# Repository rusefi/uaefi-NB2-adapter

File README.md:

# ABANDONED, NOT TESTED

# uaefi-adapter-template

To be used with https://github.com/rusefi/uaefi

powerted by [rusEFI firmware](https://github.com/rusefi/rusefi)

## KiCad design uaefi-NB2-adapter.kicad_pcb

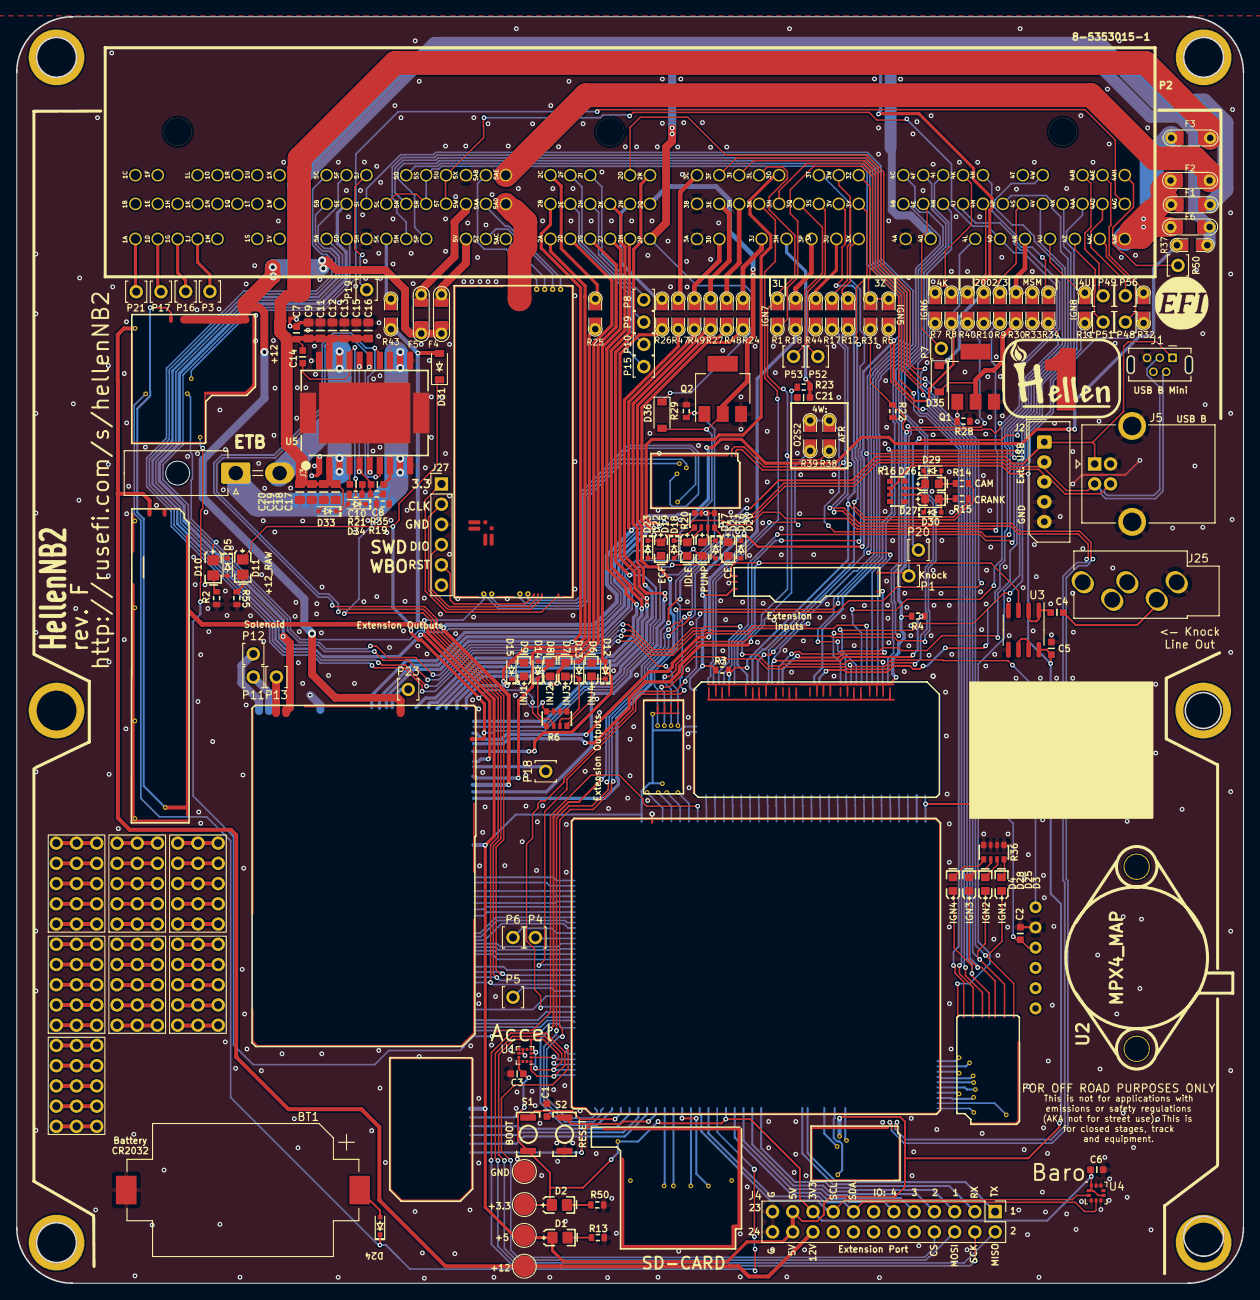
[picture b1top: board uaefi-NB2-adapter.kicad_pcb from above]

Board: 2 copper layers, 154.0 x 159.0 mm, 188 parts (1 on the bottom side), 296 nets.

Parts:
BT1: BATTERY_CR2032; BatteryHolder_Keystone_1060_1x2032
C1, C2, C3, C5, C6, C7, C21: 100n; C0603
C4: 10u; C0603
C8: 6.8n; C0603
C9, C11, C12, C13, C15, C16, C17, C18, C19, C20: 10u; C0805
C10: 10n; C0603
C14: 220n; C0603
D1, D2, D10, D11: LED-GREEN-0805; LED-0805
D3, D4, D25, D28: LED-BLUE-0603; LED-0603
D5, D12, D13, D14, D15, D20, D21, D22, D23, D24, D29, D30, D33, D34: 1N4148WS; SOD-323
D6, D7, D8, D9: LED-RED-0603; LED-0603
D16, D17, D18, D19, D26, D27: LED-WHITE-0603; LED-0603
D31, D35, D36: B5819W; SOD-123
F1, F2, F3, F4, F5, F6: Fuse-Pad-Pad; PAD-1206-PAD
G1, G3: LOGO
G2: DISCLAIMER; Off_Road_Disclaimer
G4, G5, G6, G7, G9, G11, G12: PROTO_AREA
J1: USB_B_Mini; USB-MINI-B-VERTICAL
J2: Conn_01x05_Male; Molex_SPOX_5267-05A_1x05_P2.50mm_Vertical
J3: MiniFit; Molex-39301020
J4: Conn_02x12_Odd_Even; PinHeader_2x12_P2.54mm_Vertical
J5: USB_B
J11, J13, J14, J15, J16, J17: Conn_01x01; MountingHole_4.5mm_Pad
J19, J20, J21, J22, J24: Conn_01x01; TestPoint_Pad_D2.0mm
J25: AudioJack3_SwitchTR; Jack_3.5mm_PJ-3250-5A
J27: Conn_01x06; PinHeader_1x06_P2.54mm_Vertical
M1: Module-input-0.1; input
M2: Module-ign8-0.2; ign8
M3: Module-mcu-0.6; mcu
M4: Module-sd-0.1; sd
M5: Module-output-0.3; output
M6: Module-dinput4-0.1; dinput4
M7: Module-stlink-0.1; stlink
M8, M13: Module-can-0.1; can
M9: Module-knock-0.1; knock
M10: Module-power12-0.2; power12
M11: Module-power5-0.2; power5
M12: Module-wbo-0.3; wbo
P1, P3, P4, P5, P6, P7, P8, P9, P10, P11, P12, P13, P15, P16, P17, P18, P19, P20, P21, P23, P48, P49, P50, P51, P52, P53, P56: Pad; PAD-TH
P2: 8-5353015-1
Q1, Q2: AUIPS2041LTR; SOT-223
R1, R5, R7, R8, R9, R10, R11, R12, R17, R18, R24, R25, R26, R27, R30, R31, R32, R33, R34, R37, R38, R39, R40, R43, R44, R47, R48, R49: Jumper-Pad-Pad; PAD-0805-PAD
R2, R55: 5.1k; R0603
R3: 4.7k; R0603
R4: 1k; R0603
R6, R16: 4.7k; R0603-4
R13: 1.6k; R0603
R14, R15, R23: 0; R0603
R19, R28, R29: 10k; R0603
R20: 20k; R0603-4
R21: 100; R0603
R22: 680k; R0603
R35: 100k; R0603
R36: 470; R0603-4
R50: 750; R0603
S1, S2: Button_SPST; SMD-2_2.9x3.9x1.7
U1: LIS2DW12TR; LGA-12_2x2mm_P0.5mm
U2: MPX4_MAP; MPX-4_MAP
U3: MCP6002-xSN; SOIC-8_3.9x4.9mm_P1.27mm
U4: LPS25HB; ST_HLGA-10_2.5x2.5mm_P0.6mm_LayoutBorder3x2y
U5: L6205PD; SO20POWER

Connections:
+3V3: C3.2, C6.2, D2.1 (A), J4.19, J21.1, M3.N16 (V33), M4.V1 (V33), M7.N2 (V33), S1.2, U1.9 (Vdd), U1.10 (Vdd_IO), U4.1 (VDDio), U4.6 (~CS), U4.10 (VDD)
+3V3_IGN: M2.V10 (V33), M3.W10 (IGN_V33)
+5V: C5.2, D1.1 (A), J4.21, J4.22, J20.1, M1.E2 (V5), M3.S1 (V5), M5.W14 (V5), M6.J1 (PULL_D1), M6.J2 (PULL_D2), M6.J3 (PULL_D3), M6.V1 (V5), M6.V6 (PULL_V5), M7.N1 (V5), M8.V1 (V5), M10.E1 (V5), M11.V2 (V5), M12.W1 (V5_IN), M13.V1 (V5), R16.2, R16.3, U3.8 (V+)
+5VA: C2.2, M1.E5 (V5A), M1.J1 (PULL_V5A), M1.J3 (PULL_RES2), M1.J7 (PULL_AUX4), M1.J8 (PULL_AUX3), M1.J15 (PULL_IAT), M1.J16 (PULL_CLT), M1.J18 (PULL_VSS), M1.J20 (PULL_O2S), M1.J21 (PULL_CRANK), M1.J24 (PULL_SENS3), M1.J26 (PULL_SENS1), M1.N1 (V5A), M3.S33 (V5A), M9.E1 (V5A), P2.12 (5S), P2.51 (5L), P2.53 (5R), P2.116 (4L), R3.1, R8.1, U2.3 (VCC)
+5V_IGN: M2.V9 (VCC), M3.W9 (IGN_V5)
+12V: J4.20, J19.1, M10.V1 (V12), M11.V1 (V12)
+12V_ETB: C7.2, C9.1, C11.1, C12.1, C13.1, C14.1, C15.1, C16.2, C17.1, C18.1, C19.2, C20.2, D33.2 (A), F3.2, U5.2 (VSA), U5.19 (VSB)
+12V_PERM: M10.V4 (V12_PERM), P2.84 (4AG)
+12V_PROT: D11.1 (A), D31.1 (K), M5.W5 (V12P), R6.1, R6.2, R6.3, R6.4, R20.1, R20.2, R20.3, R20.4
+12V_RAW: D35.1 (K), D36.1 (K), F1.2, F4.2, F5.2, M5.S11 (V12_RAW), M10.E2 (V12_RAW), P2.106 (2P), R10.2
/1A: P2.85 (1A), P21.1
/1D: P2.86 (1D), P17.1
/1G: P2.87 (1G), P16.1
/1J: P2.88 (1J), P3.1
/2C: P2.17 (2C), R25.2
/2E: P2.59 (2E), P15.1
/2F: P2.18 (2F), P10.1
/2H: P2.60 (2H), P9.1
/2I: P2.19 (2I), P8.1
/2N: P2.62 (2N), R26.2
/3C: P2.22 (3C), R47.2
/3D: P2.108 (3D), R49.2
/3H: P2.66 (3H), R48.2
/3J: P2.109 (3J), R24.2
/3Q: P2.69 (3Q), P53.1
/3S: P2.70 (3S), P52.1
/3U: P2.112 (3U), R44.2
/3W: P2.28 (3W), R17.1
/3X: P2.113 (3X), R12.1
/3Z: P2.29 (3Z), R5.2, R31.2
/4AB: P2.37 (4AB), P49.1
/4AC: P2.121 (4AC), P48.1
/4AD: P2.83 (4AD), P56.1
/4AE: P2.38 (4AE), R32.2
/4AF: F1.1, F2.2, F3.1, F6.2, P2.122 (4AF)
/4E: P2.74 (4E), P7.1
/4K: P2.33 (4K), R7.2, R8.2
/4M: P2.77 (4M), R40.2
/4S: P2.79 (4S), R9.2
/4Z: P2.120 (4Z), P51.1
/5AE: F2.1, P2.16 (5AE)
/5J: P2.10 (5J), P19.1
/5K: P2.95 (5K), R43.2
/+ETB: M3.E15 (OUT_PWM3), M5.W32 (SOLENOID_A2), U5.7 (IN2A), U5.15 (IN2B)
/-ETB: M3.E16 (OUT_PWM4), M5.W31 (SOLENOID_B1), U5.6 (IN1A), U5.14 (IN1B)
/AC_RELAY: M3.E9 (OUT_IO6), M5.W37 (LOW8_HIGH2)
/AC_SW: M1.N8 (AUX3), M3.S26 (IN_AUX3)
/AFR: M1.N18 (O2S), M3.S16 (IN_O2S)
/ALTERN: M3.E19 (OUT_PWM7), M5.W28 (PP1)
/BOOT0: M3.N28 (BOOT0), S1.1
/BRAKE: M1.N6 (RES1), M3.S28 (IN_RES1)
/CAM: M1.N19 (CAM), M3.S15 (IN_CAM)
/CAN+: M8.S2 (CANH), M13.S2 (CANH), R17.2
/CAN-: M8.S1 (CANL), M13.S1 (CANL), R12.2
/CANIST: M3.E21 (OUT_IO7), M5.W26 (LOW10)
/CAN_RX: M3.N2 (CAN_RX), M13.V6 (CAN_RX)
/CAN_TX: M3.N3 (CAN_TX), M13.V5 (CAN_TX)
/CAN_VIO: M3.N1 (CAN_VIO), M13.V2 (CAN_VIO)
/CE: M3.E22 (OUT_IO8), M5.W25 (LOW6_DIODE)
/CLT: M1.N16 (CLT), M3.S18 (IN_CLT)
/CLUTCH: M3.S4 (IN_D2), M6.W3 (OUT_D2)
/CRANK: M1.N21 (CRANK), M3.S13 (IN_CRANK)
/D3: M3.S5 (IN_D3), M6.W2 (OUT_D3)
/D4: M3.S6 (IN_D4), M6.W1 (OUT_D4)
/DIGITAL: M3.S3 (IN_D1), M6.W4 (OUT_D1)
/ECF_RELAY: M3.E28 (OUT_PWM8), M5.W21 (LOW1)
/EGR_BOOST: M1.N7 (AUX4), M3.S27 (IN_AUX4)
/ETB_EN: M3.E14 (OUT_PWM2), M5.W33 (SOLENOID_A1), R19.2, R35.2
/EXT_I2C_SCL: J4.17, M3.N19 (I2C_SCL), U4.2 (SCL/SCLK)
/EXT_I2C_SDA: J4.15, M3.N18 (I2C_SDA), U4.4 (SDA/MOSI)
/EXT_IO1: J4.5, M3.N12 (IO1)
/EXT_IO2: J4.7, M3.N13 (IO2)
/EXT_IO3: J4.9, M3.N14 (IO3)
/EXT_IO4: J4.11, M3.N15 (IO4)
/EXT_SPI_CS: M3.E4 (SPI1_CS1), U1.2 (~CS)
/EXT_SPI_CS2: J4.8, M3.E5 (SPI1_CS2)
/EXT_SPI_MISO: J4.2, M3.E2 (SPI1_MISO), U1.3 (SA0/SDO)
/EXT_SPI_MOSI: J4.6, M3.E3 (SPI1_MOSI), U1.4 (SDA/SDI)
/EXT_SPI_SCK: J4.4, M3.E1 (SPI1_SCK), U1.1 (SCL/SPC)
/IAT: M1.N15 (IAT), M3.S19 (IN_IAT)
/IDLE: M3.E18 (OUT_PWM6), Q2.1 (IN), R29.1
/IGN1: M2.V8 (IGN1), M3.W1 (OUT_IGN1)
/IGN2: M2.V7 (IGN2), M3.W2 (OUT_IGN2)
/IGN3: M2.V6 (IGN3), M3.W3 (OUT_IGN3)
/IGN4: M2.V5 (IGN4), M3.W4 (OUT_IGN4)
/IGN5: M2.V4 (IGN5), M3.W5 (OUT_IGN5)
/IGN6: M2.V3 (IGN6), M3.W6 (OUT_IGN6)
/IGN7: M2.V2 (IGN7), M3.W7 (OUT_IGN7)
/IGN8: M2.V1 (IGN8), M3.W8 (OUT_IGN8)
/INJ1: M3.E25 (OUT_INJ1), M5.W24 (INJ1)
/INJ2: M3.E26 (OUT_INJ2), M5.W23 (INJ2)
/INJ3: M3.E29 (OUT_INJ3), M5.W20 (INJ3)
/INJ4: M3.E30 (OUT_INJ4), M5.W19 (INJ4)
/INJ5: M3.E31 (OUT_INJ5), M5.W18 (INJ5)
/INJ6: M3.E32 (OUT_INJ6), M5.W17 (INJ6)
/INJ7: M3.E33 (OUT_INJ7), M5.W16 (INJ7)
/INJ8_BOOST: M3.E34 (OUT_INJ8), M5.W15 (INJ8)
/IN_AC_PRESSURE: M1.S17 (IN_AUX1), P2.31 (4F), R22.1
/IN_AFR: M1.S25 (IN_O2S2), P2.25 (3L), R1.2, R38.2
/IN_BRAKE: M1.S23 (IN_RES1), P2.73 (4B)
/IN_CAM: M1.S5 (IN_CAM), P2.71 (3V), R3.2, R14.1
/IN_CLT: M1.S15 (IN_CLT), P2.78 (4P)
/IN_CLUTCH: M6.V3 (IN_D2), P2.32 (4I)
/IN_CRANK: M1.S8 (IN_CRANK), P2.72 (3Y), R15.1
/IN_D4: M6.V5 (IN_D4), P2.8 (5C)
/IN_DIGITAL: M6.V2 (IN_D1), P2.50 (5I)
/IN_EGR_BOOST: M1.S20 (IN_AUX3), R32.1
/IN_IAT: M1.S16 (IN_IAT), R33.1, R34.1
/IN_KNOCK: M1.S7 (IN_KNOCK), M9.E3 (OUT_KNOCK), U3.3 (+)
/IN_KNOCK_RAW: M9.W1 (IN_KNOCK), P1.1, R40.1
/IN_MAP1: M1.S11 (IN_MAP1), P2.92 (5A), R4.1
/IN_MAP2: M1.S12 (IN_MAP2), P2.119 (4U), R11.2
/IN_MAP3: M1.S19 (IN_MAP3), U2.1 (VOUT)
/IN_NEUTRAL: M6.V4 (IN_D3), P2.75 (4H)
/IN_O2S2: M1.S1 (IN_SENS1), R39.2
/IN_O2S3: M1.S4 (IN_SENS4), P2.82 (4AA)
/IN_PPS: M1.S24 (IN_PPS), P2.97 (5P)
/IN_PPS2: M1.S18 (IN_AUX2), P2.96 (5M)
/IN_RES3: M1.S22 (IN_RES3), P2.48 (5B)
/IN_SENS2: M1.S2 (IN_SENS2), P2.67 (3K)
/IN_SENS3: M1.S3 (IN_SENS3), P2.93 (5D)
/IN_STEERING: M1.S26 (IN_RES2), P2.30 (4C)
/IN_TPS: M1.S10 (IN_TPS), P2.11 (5O), P2.80 (4V)
/IN_TPS2: M1.S9 (IN_O2S), P2.52 (5N)
/IN_VIGN: D5.1 (K), D10.1 (A), M10.V3 (IN_VIGN), R9.1, R10.1
/IN_VSS: M1.S6 (IN_VSS), P2.27 (3T)
/IN_VTCS: M1.S21 (IN_AUX4), P2.76 (4J)
/IO4: M3.E23 (OUT_IO4), P4.1
/IO12: M3.E13 (OUT_IO12), P5.1
/IO13: M3.E24 (OUT_IO13), P6.1
/KNOCK: M1.N22 (KNOCK), M3.S12 (IN_KNOCK)
/LOW7_HIGH1: M3.E7 (OUT_IO5), M5.W39 (LOW7_HIGH1)
/MAIN: M3.E6 (OUT_IO3), M5.W40 (LOW5_MAIN)
/MAP1: M1.N14 (MAP1), M3.S20 (IN_MAP1)
/MAP2: M1.N13 (MAP2), M3.S21 (IN_MAP2)
/MAP3: M1.N12 (MAP3), M3.S22 (IN_MAP3)
/NRESET: C1.2, M3.N24 (nReset), M7.N6 (nReset), S2.1
/O2H: M3.E8 (OUT_IO1), M5.W38 (LOW3_DUAL)
/O2H2: M3.E12 (OUT_IO2), M5.W34 (LOW4_DUAL)
/OUT_AC_RELAY: M5.S12 (OUT_LOW8_PULLUP), P2.61 (2K)
/OUT_ALTERNATOR: C21.2, P2.110 (3M), R23.2
/OUT_CANIST: M5.W2 (OUT_LOW10), R27.2
/OUT_CHECK_ENGINE: D16.2 (K), D20.2 (A), M5.W3 (OUT_LOW6_DIODE), P2.21 (2R)
/OUT_ECF_RELAY: D19.2 (K), D23.2 (A), M5.S8 (OUT_LOW1), P2.58 (2B)
/OUT_ETB+: J3.2, U5.3 (OUT2A), U5.18 (OUT2B)
/OUT_ETB-: J3.1, U5.9 (OUT1A), U5.12 (OUT1B)
/OUT_HIGH1: M5.W8 (OUT_HIGH1), P2.9 (5F)
/OUT_HIGH2: M5.S9 (OUT_HIGH2), P23.1
/OUT_IDLE: D18.2 (K), D22.2 (A), D36.2 (A), P2.63 (2Q), Q2.2 (D)
/OUT_IGN1: D3.1 (A), M2.S8 (OUT_IGN1), P2.23 (3F)
/OUT_IGN2: D25.1 (A), M2.S7 (OUT_IGN2), P2.24 (3I)
/OUT_IGN3: D28.1 (A), M2.S6 (OUT_IGN3), P2.20 (2O)
/OUT_IGN4: D4.1 (A), M2.S5 (OUT_IGN4), P2.68 (3N)
/OUT_IGN5: M2.S4 (OUT_IGN5), R5.1
/OUT_IGN6: M2.S3 (OUT_IGN6), R7.1
/OUT_IGN7: M2.S2 (OUT_IGN7), R1.1
/OUT_IGN8: M2.S1 (OUT_IGN8), R11.1
/OUT_INJ1: D9.2 (K), D15.2 (A), M5.S18 (OUT_INJ1), P2.101 (2A)
/OUT_INJ2: D8.2 (K), D14.2 (A), M5.S16 (OUT_INJ2), P2.102 (2D)
/OUT_INJ3: D7.2 (K), D13.2 (A), M5.S17 (OUT_INJ3), P2.103 (2G)
/OUT_INJ4: D6.2 (K), D12.2 (A), M5.W7 (OUT_INJ4), P2.104 (2J)
/OUT_INJ5: M5.W10 (OUT_INJ5), R25.1
/OUT_INJ6: M5.S15 (OUT_INJ6), R26.1
/OUT_INJ7: M5.W12 (OUT_INJ7), R47.1
/OUT_INJ8_BOOST: D31.2 (A), M5.W11 (OUT_INJ8), R37.1, R43.1, R49.1
/OUT_LOW7_PULLUP: M5.W9 (OUT_LOW7_PULLUP), P18.1
/OUT_MAIN_RELAY: M5.W13 (OUT_LOW5_MAIN), R48.1
/OUT_O2H: M5.S7 (OUT_LOW3_DUAL), R24.1
/OUT_O2H2: M5.W4 (OUT_LOW4_DUAL), R18.1
/OUT_PUMP_RELAY: D17.2 (K), D21.2 (A), M5.S14 (OUT_LOW9), P2.105 (2M)
/OUT_SOLENOID_A1: M5.S1 (OUT_SOLENOID_A1), P12.1
/OUT_SOLENOID_A2: M5.S2 (OUT_SOLENOID_A2), P11.1
/OUT_SOLENOID_B1: M5.S4 (OUT_SOLENOID_B1), P13.1
/OUT_SOLENOID_B2: M5.S5 (OUT_SOLENOID_B2), P2.49 (5E)
/OUT_TACH: M5.S6 (OUT_PP2), P2.26 (3O)
/OUT_VVT: D35.2 (A), Q1.2 (D), R30.1
/PPS: M1.N5 (PPS), M3.S29 (IN_PPS)
/PPS2: M1.N9 (AUX2), M3.S25 (IN_AUX2)
/PRESSURE: M1.N10 (AUX1), M3.S24 (IN_AUX1)
/PUMP: M3.E20 (OUT_IO11), M5.W27 (LOW9)
/RES3: M1.N11 (RES3), M3.S23 (IN_RES3)
/SD_CS: M3.N23 (SPI2_CS), M4.V4 (SD_CS)
/SD_MISO: M3.N21 (SPI2_MISO), M4.V7 (SD_MISO)
/SD_MOSI: M3.N22 (SPI2_MOSI), M4.V5 (SD_MOSI)
/SD_SCK: M3.N20 (SPI2_SCK), M4.V6 (SD_SCK)
/SENS1: M1.N26 (SENS1), M3.S8 (IN_SENS1)
/SENS2: M1.N25 (SENS2), M3.S9 (IN_SENS2)
/SENS3: M1.N24 (SENS3), M3.S10 (IN_SENS3)
/SENS4: M1.N23 (SENS4), M3.S11 (IN_SENS4)
/SOLENOID_B2: M3.E17 (OUT_PWM5), M5.W30 (SOLENOID_B2)
/STEERING: M1.N3 (RES2), M3.S31 (IN_RES2)
/TACH: M3.E27 (OUT_PWM1), M5.W22 (PP2)
/TPS: M1.N17 (TPS), M3.S17 (IN_TPS)
/TPS2: M1.N4 (O2S2), M3.S30 (IN_O2S2)
/UART_EXT_RX: J4.3, M3.N7 (UART2_RX)
/UART_EXT_TX: J4.1, M3.N6 (UART2_TX)
/USB+: J1.3 (D+), J2.3, J5.3 (D+), M3.N30 (USB1P)
/USB-: J1.2 (D-), J2.2, J5.2 (D-), M3.N31 (USB1M)
/VBAT: D24.1 (K), M3.N17 (VBAT), M10.V2 (VBAT)
/VBUS: J1.1 (VBUS), J2.1, J5.1 (VBUS), M3.N29 (VBUS)
/VIGN: M3.S7 (VIGN), M10.V5 (VIGN)
/VREF2: M1.S13 (VREF2), M9.W2 (VREF)
/VSS: M1.N20 (VSS), M3.S14 (IN_VSS)
/VVT: M3.E10 (OUT_IO10), Q1.1 (IN), R28.1
/WBO_H-: M12.E5 (LSU_H+), P2.57 (5AD)
/WBO_Ip: M12.E3 (LSU_Ip), P2.100 (5AC)
/WBO_R_Trim: M12.E4 (LSU_Rtrim), P2.15 (5AB)
/WBO_Vs: M12.E1 (LSU_Un), P2.56 (5AA)
/WBO_Vs/Ip: M12.E2 (LSU_Vm), P2.99 (5Z)
GND: BT1.2 (-), C1.1, C2.1, C3.1, C5.1, C6.1, C7.1, C8.2, C9.2, C11.2, C12.2, C13.2, C15.2, C16.1, C17.2, C18.2, C19.1, C20.1, C21.1, J1.5 (GND), J1.6 (Shield), J2.4, J2.5, J4.23, J4.24, J5.4 (GND), J5.5 (Shield), J22.1, J24.1, J25.S, J27.3, M1.E1 (GND), M2.G (GND), M3.S2 (GND), M4.G (GND), M4.V2 (GND), M4.V3 (GND), M5.G (GND), M5.S3 (GND), M6.G (GND), M6.J4 (PULL_D4), M7.G (GND), M8.E1 (GND), M9.E2 (GND), M10.S1 (GND), M11.G (GND), M12.E6 (LSU_H-), M12.G (GND), M13.E1 (GND), P2.14 (5X), P2.64 (3B), P2.94 (5H), P2.107 (3A), P2.114 (4A), Q1.3 (S), Q2.3 (S), R2.2, R13.2, R19.1, R28.2, R29.2, R36.1, R36.2, R36.3, R36.4, R50.2, R55.2, S2.2, U1.6 (GND), U1.7 (RES), U1.8 (GND), U2.2 (GND), U3.4 (V-), U3.5 (+), U4.3 (GND), U4.5 (SA0/MISO), U4.8 (GND), U4.9 (GND), U5.1 (GND@1), U5.8 (SENSEA), U5.10 (GND@2), U5.11 (GND@3), U5.13 (SENSEB), U5.20 (GND@4), U5.SLUG1 (SLUG@1), U5.SLUG2 (SLUG@2), U5.SLUG3 (SLUG@3)
GNDA: M1.J2 (PULL_GNDA), M1.J4 (PULL_O2S2), M1.J5 (PULL_PPS), M1.J6 (PULL_RES1), M1.J9 (PULL_AUX2), M1.J11 (PULL_RES3), M1.J12 (PULL_MAP3), M1.J13 (PULL_MAP2), M1.J19 (PULL_TPS), M1.J22 (PULL_KNOCK), M1.J23 (PULL_SENS4), M1.J25 (PULL_SENS2), M1.N2 (GNDA), M3.S32 (GNDA), P2.13 (5U), P2.54 (5T), P2.117 (4O), R4.2, R22.2, R31.1
unnamed: BT1.1 (+), D24.2 (A)
unnamed: C4.1, J25.T
unnamed: C4.2, U3.1, U3.2 (-)
unnamed: C8.1, R35.1, U5.5 (ENA), U5.16 (ENB)
unnamed: C10.1, R21.1
unnamed: C10.2, U5.4 (VCP)
unnamed: C14.2, D34.1 (K), U5.17 (VBOOT)
unnamed: D1.2 (K), R13.1
unnamed: D2.2 (K), R50.1
unnamed: D3.2 (K), R36.8
unnamed: D4.2 (K), R36.5
unnamed: D5.2 (A), D10.2 (K), R2.1
unnamed: D11.2 (K), R55.1
unnamed: D6.1 (A), D12.1 (K), R6.8
unnamed: D7.1 (A), D13.1 (K), R6.7
unnamed: D8.1 (A), D14.1 (K), R6.6
unnamed: D9.1 (A), D15.1 (K), R6.5
unnamed: D16.1 (A), D20.1 (K), R20.8
unnamed: D17.1 (A), D21.1 (K), R20.7
unnamed: D18.1 (A), D22.1 (K), R20.6
unnamed: D19.1 (A), D23.1 (K), R20.5
unnamed: D25.2 (K), R36.7
unnamed: D26.1 (A), D29.1 (K), R16.7
unnamed: D26.2 (K), D29.2 (A), R14.2
unnamed: D27.1 (A), D30.1 (K), R16.6
unnamed: D27.2 (K), D30.2 (A), R15.2
unnamed: D28.2 (K), R36.6
unnamed: D33.1 (K), D34.2 (A), R21.2
unnamed: F4.1, P2.98 (5V)
unnamed: F5.1, P2.55 (5W)
unnamed: F6.1, P2.115 (4D), R37.2
unnamed: G4.1, G4.6, G4.11
unnamed: G4.5, G4.10, G4.15
unnamed: G4.2, G4.7, G4.12
unnamed: G4.3, G4.8, G4.13
unnamed: G4.4, G4.9, G4.14
unnamed: G5.1, G5.6, G5.11
unnamed: G5.5, G5.10, G5.15
unnamed: G5.2, G5.7, G5.12
unnamed: G5.3, G5.8, G5.13
unnamed: G5.4, G5.9, G5.14
unnamed: G6.1, G6.6, G6.11
unnamed: G6.5, G6.10, G6.15
unnamed: G6.2, G6.7, G6.12
unnamed: G6.3, G6.8, G6.13
unnamed: G6.4, G6.9, G6.14
unnamed: G7.1, G7.6, G7.11
unnamed: G7.5, G7.10, G7.15
unnamed: G7.2, G7.7, G7.12
unnamed: G7.3, G7.8, G7.13
unnamed: G7.4, G7.9, G7.14
unnamed: G9.1, G9.6, G9.11
unnamed: G9.5, G9.10, G9.15
unnamed: G9.2, G9.7, G9.12
unnamed: G9.3, G9.8, G9.13
unnamed: G9.4, G9.9, G9.14
unnamed: G11.1, G11.6, G11.11
unnamed: G11.5, G11.10, G11.15
unnamed: G11.2, G11.7, G11.12
unnamed: G11.3, G11.8, G11.13
unnamed: G11.4, G11.9, G11.14
unnamed: G12.1, G12.6, G12.11
unnamed: G12.5, G12.10, G12.15
unnamed: G12.2, G12.7, G12.12
unnamed: G12.3, G12.8, G12.13
unnamed: G12.4, G12.9, G12.14
unnamed: J27.1, M12.W8 (V33_OUT)
unnamed: J27.2, M12.W7 (SWCLK)
unnamed: J27.4, M12.W6 (SWDIO)
unnamed: J27.5, M12.W5 (nReset)
unnamed: M3.N25 (SWCLK), M7.N5 (SWCLK)
unnamed: M3.N26 (SWDIO), M7.N4 (SWDIO)
unnamed: M3.N27 (SWO), M7.N3 (SWO)
unnamed: M5.W6 (OUT_PP1), R23.1
unnamed: M8.V2 (CAN_VIO), M12.W2 (CAN_VIO)
unnamed: M8.V6 (CAN_RX), M12.W3 (CAN_RX)
unnamed: M8.V5 (CAN_TX), M12.W4 (CAN_TX)
unnamed: P2.34 (4N), R34.2
unnamed: P2.36 (4W), R38.1, R39.1
unnamed: P2.39 (4AH), P50.1
unnamed: P2.65 (3E), R27.1
unnamed: P2.81 (4X), P20.1
unnamed: P2.111 (3P), R18.2
unnamed: P2.118 (4R), R30.2, R33.2
unnamed: U3.6 (-), U3.7

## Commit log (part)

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2024-02-21 GHA says update hellen-one
2024-02-22 GHA says update kicad6-libraries
